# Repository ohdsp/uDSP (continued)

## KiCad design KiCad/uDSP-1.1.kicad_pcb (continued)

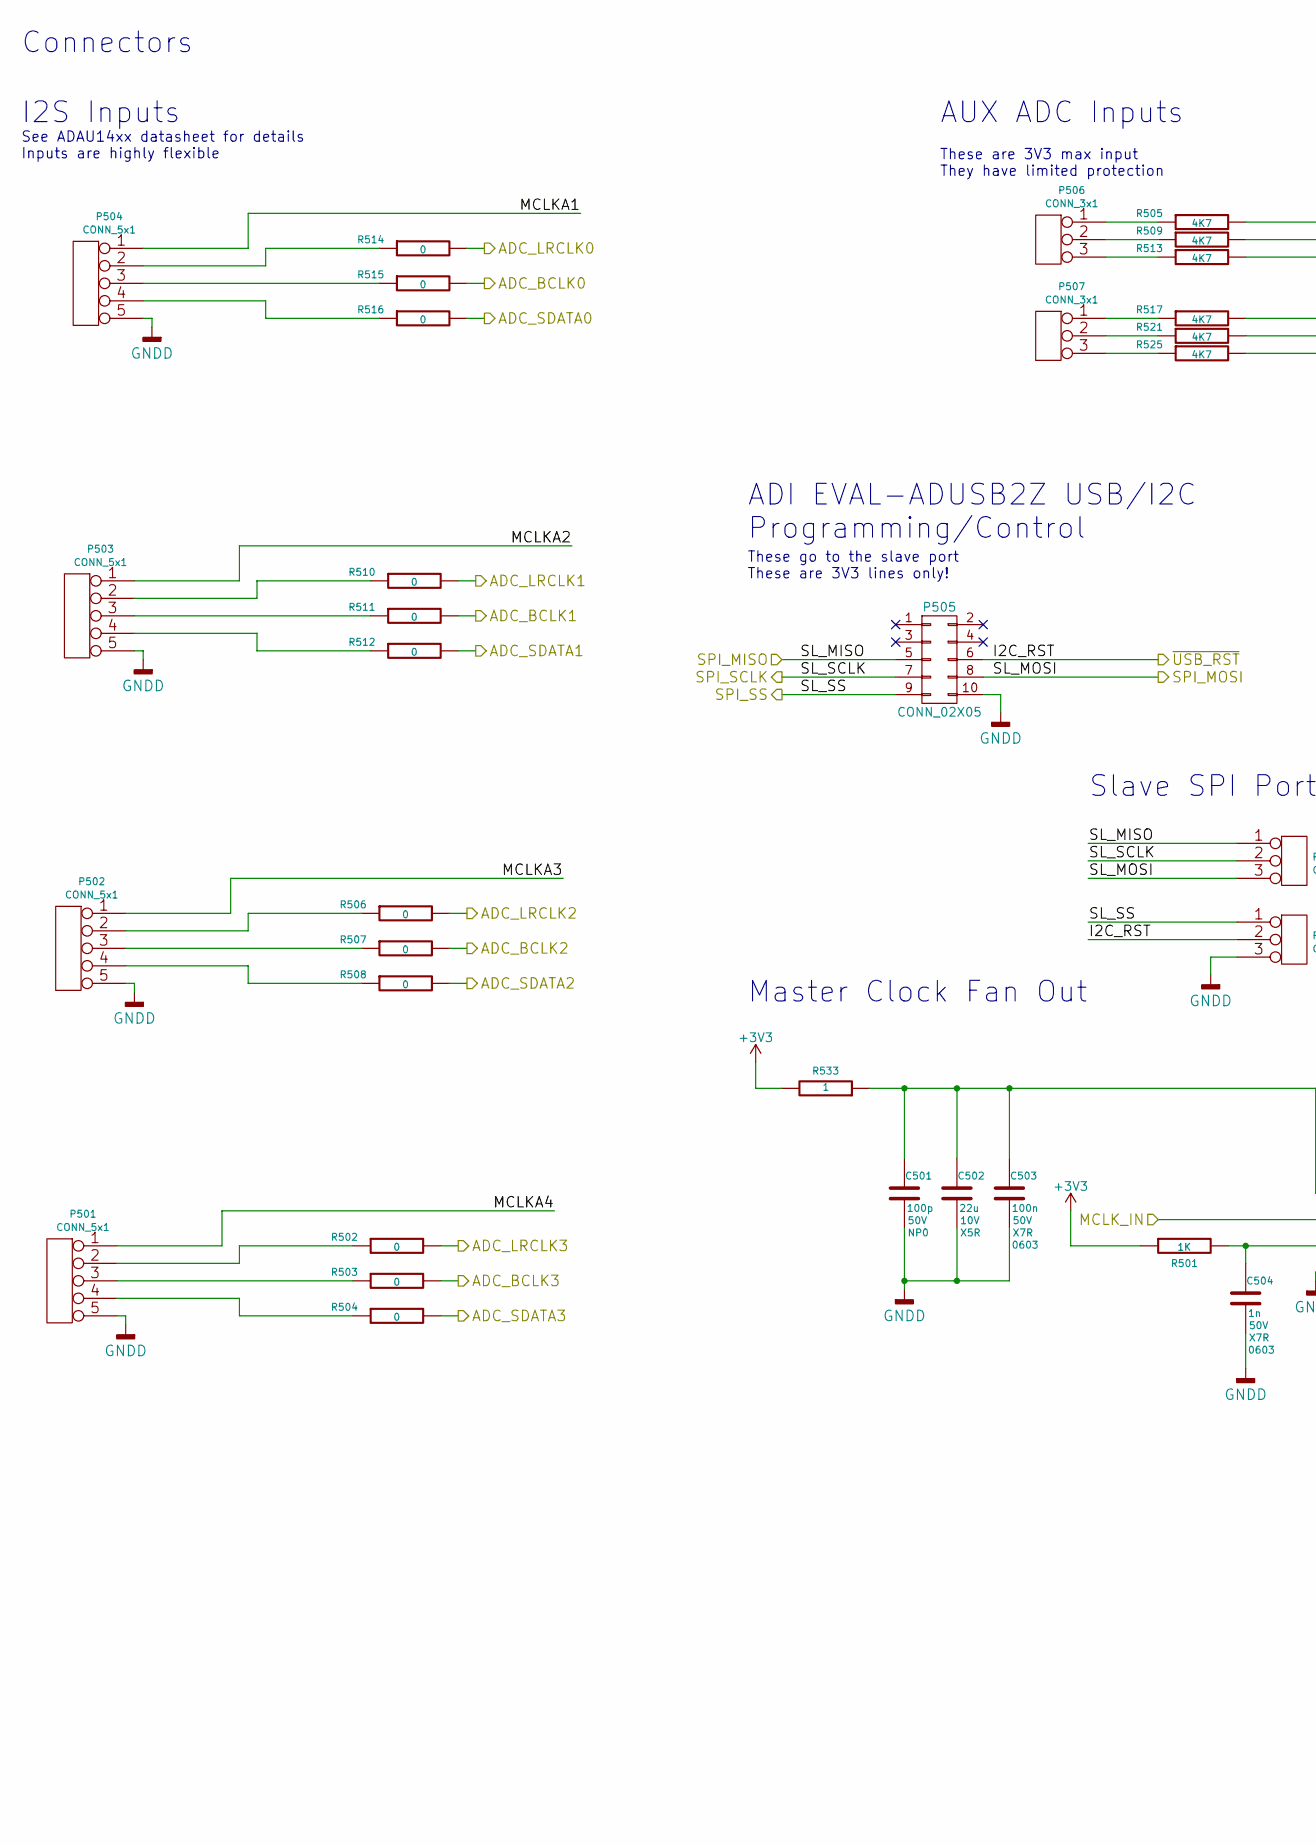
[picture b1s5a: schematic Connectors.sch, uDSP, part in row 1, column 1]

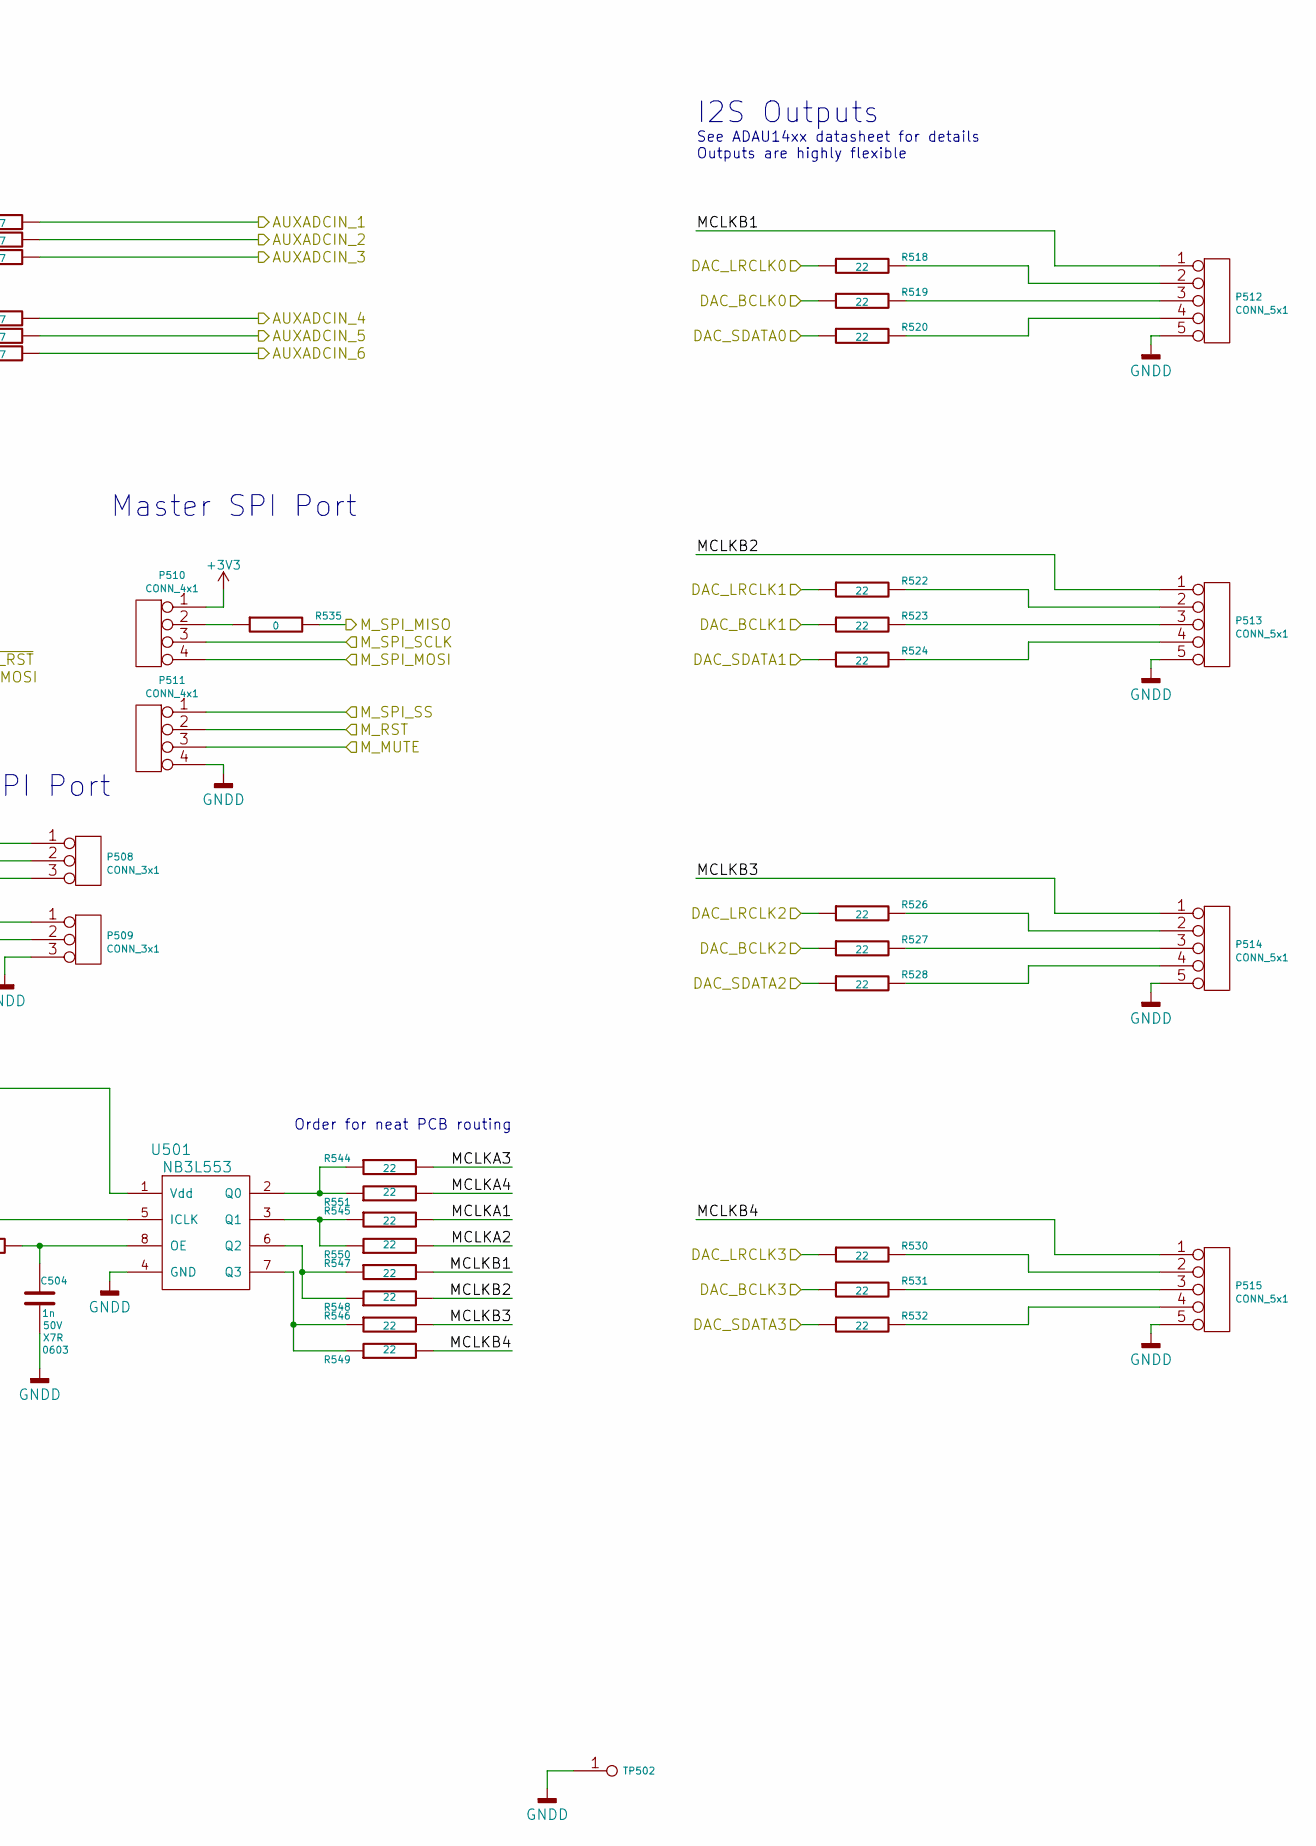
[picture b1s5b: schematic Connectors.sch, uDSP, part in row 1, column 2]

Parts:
C501: 100p; SMD-0603; Voltage 50V; Tolerance 5%
C502: 22u; SMD-0603; Voltage 10V; Tolerance 10%
C503: 100n; SMD-0603; Voltage 50V; Tolerance 10%
C504: 1n; SMD-0603; Voltage 50V; Tolerance 10%
P501, P502, P503, P504, P512, P513, P514, P515: CONN_5x1; CONN_SIL_5_1MM
P505: CONN_02X05; CONN_DIL_2X5_BOX_1MM
P506, P507, P508, P509: CONN_3x1; CONN_SIL_3_1MM
P510, P511: CONN_4x1; CONN_SIL_4_1MM
R501: 1K; SMD-0603; Tolerance 1%
R502, R503, R504, R506, R507, R508, R510, R511, R512, R514, R515, R516, R535: 0; SMD-0603; Tolerance 1%
R505, R509, R513, R517, R521, R525: 4K7; SMD-0603; Tolerance 1%
R518, R519, R520, R522, R523, R524, R526, R527, R528, R530, R531, R532, R544, R545, R546, R547, R548, R549, R550, R551: 22; SMD-0603; Tolerance 1%
R533: 1; SMD-0603; Tolerance 1%
TP502: PIN; TP-TH-1mm
U501: NB3L553; IC_SOIC_8

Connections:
/AUXADC1: R505.2; also elsewhere on the board
/AUXADC2: R509.2; also elsewhere on the board
/AUXADC3: R513.2; also elsewhere on the board
/AUXADC4: R517.2; also elsewhere on the board
/AUXADC5: R521.2; also elsewhere on the board
/AUXADC6: R525.2; also elsewhere on the board
/Connectors/MCLKA1: P504.1, R545.2
/Connectors/MCLKA2: P503.1, R550.2
/Connectors/MCLKA3: P502.1, R544.2
/Connectors/MCLKA4: P501.1, R551.2
/Connectors/MCLKB1: P512.1, R547.2
/Connectors/MCLKB2: P513.1, R548.2
/Connectors/MCLKB3: P514.1, R546.2
/Connectors/MCLKB4: P515.1, R549.2
/GLB_RESET: P511.2; also elsewhere on the board
/IN_BCLK0: R515.2; also elsewhere on the board
/IN_BCLK1: R511.2; also elsewhere on the board
/IN_BCLK2: R507.2; also elsewhere on the board
/IN_BCLK3: R503.2; also elsewhere on the board
/IN_LRCLK0: R514.2; also elsewhere on the board
/IN_LRCLK1: R510.2; also elsewhere on the board
/IN_LRCLK2: R506.2; also elsewhere on the board
/IN_LRCLK3: R502.2; also elsewhere on the board
/IN_SDATA0: R516.2; also elsewhere on the board
/IN_SDATA1: R512.2; also elsewhere on the board
/IN_SDATA2: R508.2; also elsewhere on the board
/IN_SDATA3: R504.2; also elsewhere on the board
/MAN_RESET: P505.6, P509.2; also elsewhere on the board
/MCLK: U501.5 (ICLK); also elsewhere on the board
/OUT_BCLK0: R519.1; also elsewhere on the board
/OUT_BCLK1: R523.1; also elsewhere on the board
/OUT_BCLK2: R527.1; also elsewhere on the board
/OUT_BCLK3: R531.1; also elsewhere on the board
/OUT_LRCLK0: R518.1; also elsewhere on the board
/OUT_LRCLK1: R522.1; also elsewhere on the board
/OUT_LRCLK2: R526.1; also elsewhere on the board
/OUT_LRCLK3: R530.1; also elsewhere on the board
/OUT_SDATA0: R520.1; also elsewhere on the board
/OUT_SDATA1: R524.1; also elsewhere on the board
/OUT_SDATA2: R528.1; also elsewhere on the board
/OUT_SDATA3: R532.1; also elsewhere on the board
/SPI_MISO: P505.5, P508.1; also elsewhere on the board
/SPI_MOSI: P505.8, P508.3; also elsewhere on the board
/SPI_M_CLK: P510.3; also elsewhere on the board
/SPI_M_CS2: P511.1; also elsewhere on the board
/SPI_M_MISO: R535.2; also elsewhere on the board
/SPI_M_MOSI: P510.4; also elsewhere on the board
/SPI_M_MUTE: P511.3; also elsewhere on the board
/SPI_SCLK: P505.7, P508.2; also elsewhere on the board
/SPI_SS: P505.9, P509.1; also elsewhere on the board
GNDD: C501.2, C502.2, C503.2, C504.2, P501.5, P502.5, P503.5, P504.5, P505.10, P509.3, P511.4, P512.5, P513.5, P514.5, P515.5, TP502.1, U501.4 (GND); also elsewhere on the board
unnamed: C501.1, C502.1, C503.1, R533.1, U501.1 (Vdd)
unnamed: C504.1, R501.2, U501.8 (OE)
unnamed: P501.2, R502.1
unnamed: P501.3, R503.1
unnamed: P501.4, R504.1
unnamed: P502.2, R506.1
unnamed: P502.3, R507.1
unnamed: P502.4, R508.1
unnamed: P503.2, R510.1
unnamed: P503.3, R511.1
unnamed: P503.4, R512.1
unnamed: P504.2, R514.1
unnamed: P504.3, R515.1
unnamed: P504.4, R516.1
unnamed: P506.1, R505.1
unnamed: P506.2, R509.1
unnamed: P506.3, R513.1
unnamed: P507.1, R517.1
unnamed: P507.2, R521.1
unnamed: P507.3, R525.1
unnamed: P510.2, R535.1
unnamed: P512.2, R518.2
unnamed: P512.3, R519.2
unnamed: P512.4, R520.2
unnamed: P513.2, R522.2
unnamed: P513.3, R523.2
unnamed: P513.4, R524.2
unnamed: P514.2, R526.2
unnamed: P514.3, R527.2
unnamed: P514.4, R528.2
unnamed: P515.2, R530.2
unnamed: P515.3, R531.2
unnamed: P515.4, R532.2
unnamed: R544.1, R551.1, U501.2 (Q0)
unnamed: R545.1, R550.1, U501.3 (Q1)
unnamed: R546.1, R549.1, U501.7 (Q3)
unnamed: R547.1, R548.1, U501.6 (Q2)

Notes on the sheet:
ADI EVAL-ADUSB2Z USB/I2C Programming/Control
AUX ADC Inputs
These go to the slave port These are 3V3 lines only!
I2S Inputs
See ADAU14xx datasheet for details Inputs are highly flexible
I2S Outputs
These are 3V3 max input They have limited protection
See ADAU14xx datasheet for details Outputs are highly flexible
Order for neat PCB routing
Master Clock Fan Out
Master SPI Port
Slave SPI Port
Connectors

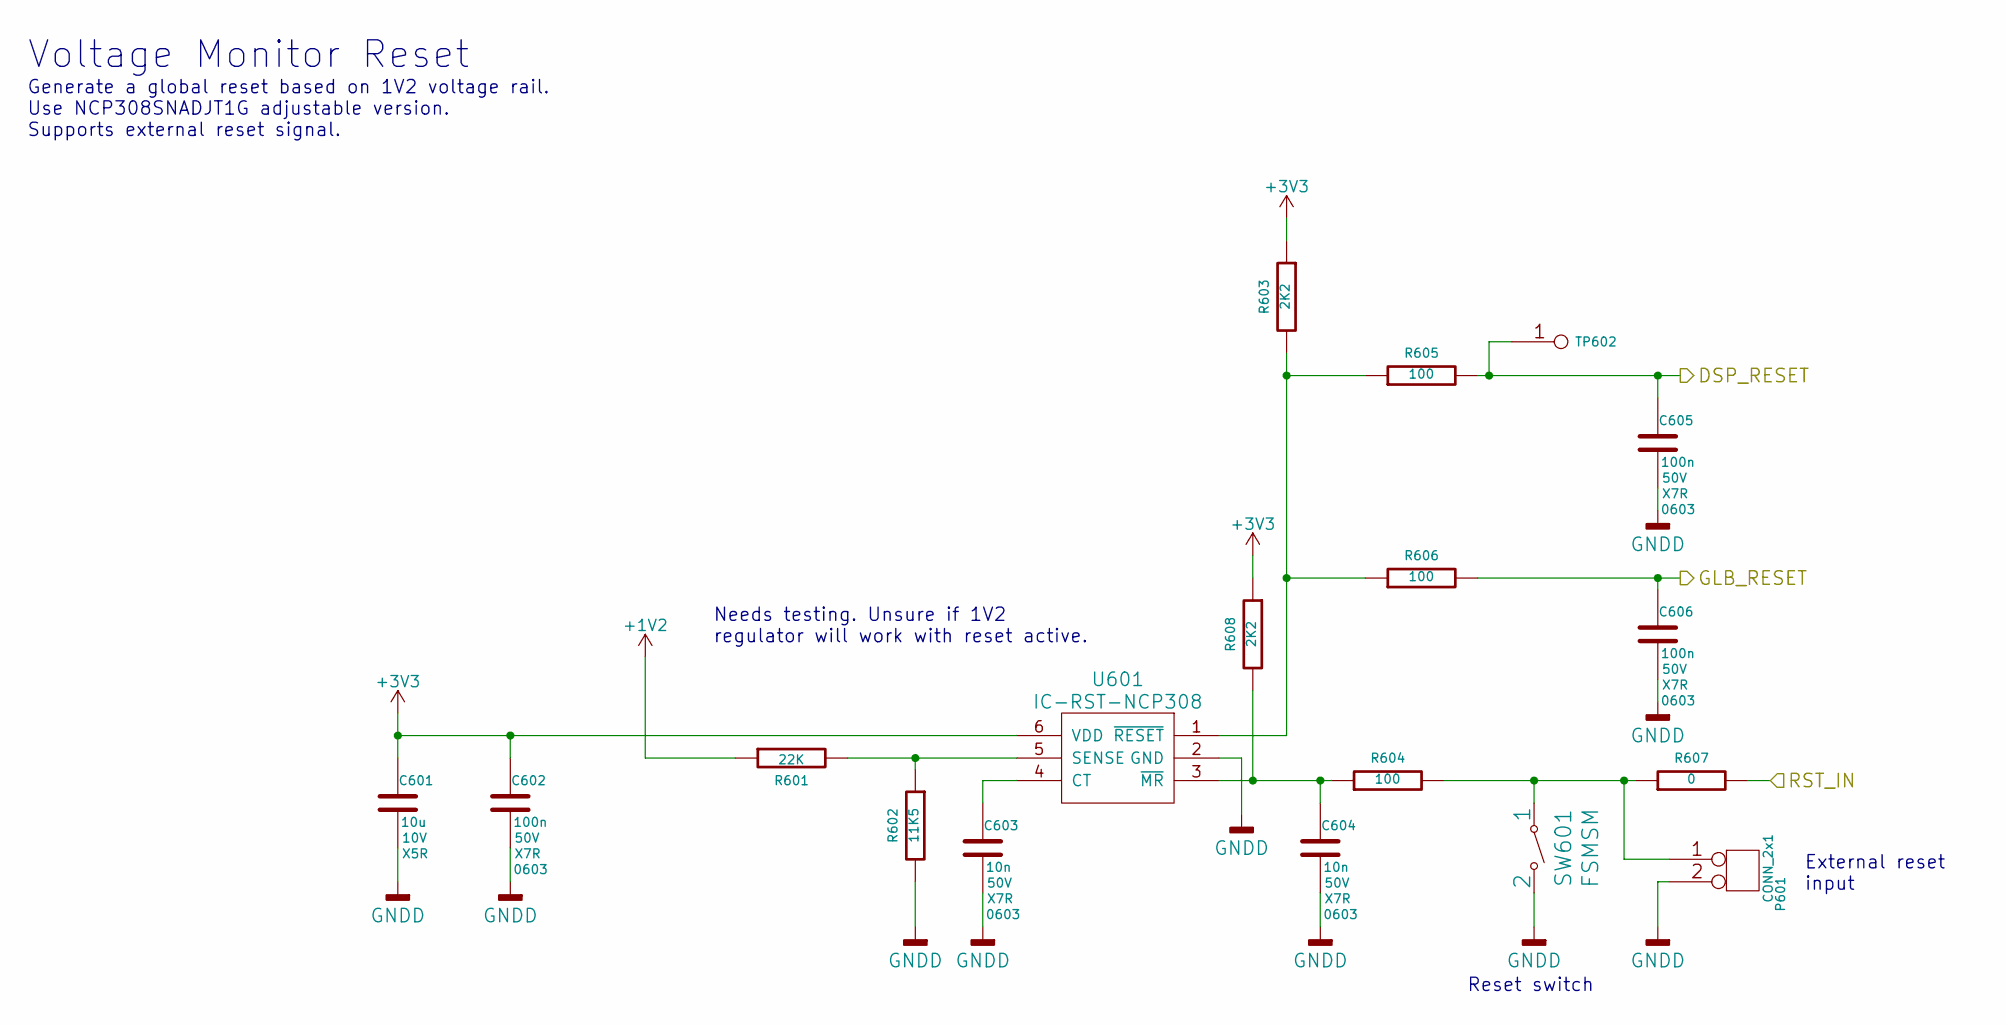
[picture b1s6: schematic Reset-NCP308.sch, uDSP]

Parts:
C601: 10u; SMD-0603; Voltage 10V; Tolerance 20%
C602, C605, C606: 100n; SMD-0603; Voltage 50V; Tolerance 10%
C603, C604: 10n; SMD-0603; Voltage 50V; Tolerance 10%
P601: CONN_2x1; CONN_SIL_2_1MM
R601: 22K; SMD-0603; Tolerance 1%
R602: 11K5; SMD-0603; Tolerance 1%
R603, R608: 2K2; SMD-0603; Tolerance 1%
R604, R605, R606: 100; SMD-0603; Tolerance 1%
R607: 0; SMD-0603; Tolerance 1%
SW601: FSMSM; SW_TACT_SMD_FSMSM
TP602: PIN; TP-1mm
U601: IC-RST-NCP308; IC-SOT23-6

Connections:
+1V2: R601.1; also elsewhere on the board
/DSP_RESET: C605.1, R605.2, TP602.1; also elsewhere on the board
/GLB_RESET: C606.1, R606.2; also elsewhere on the board
/MAN_RESET: R607.2; also elsewhere on the board
GNDD: C601.2, C602.2, C603.2, C604.2, C605.2, C606.2, P601.2, R602.2, SW601.2, U601.2 (GND); also elsewhere on the board
unnamed: C603.1, U601.4 (CT)
unnamed: C604.1, R604.1, R608.2, U601.3 (~MR)
unnamed: P601.1, R604.2, R607.1, SW601.1
unnamed 126: R601.2, R602.1, U601.5 (SENSE); also elsewhere on the board
unnamed: R603.2, R605.1, R606.1, U601.1 (~RESET)

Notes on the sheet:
Generate a global reset based on 1V2 voltage rail. Use NCP308SNADJT1G adjustable version. Supports external reset signal.
Voltage Monitor Reset
External reset input
Needs testing. Unsure if 1V2 regulator will work with reset active.
Reset switch

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
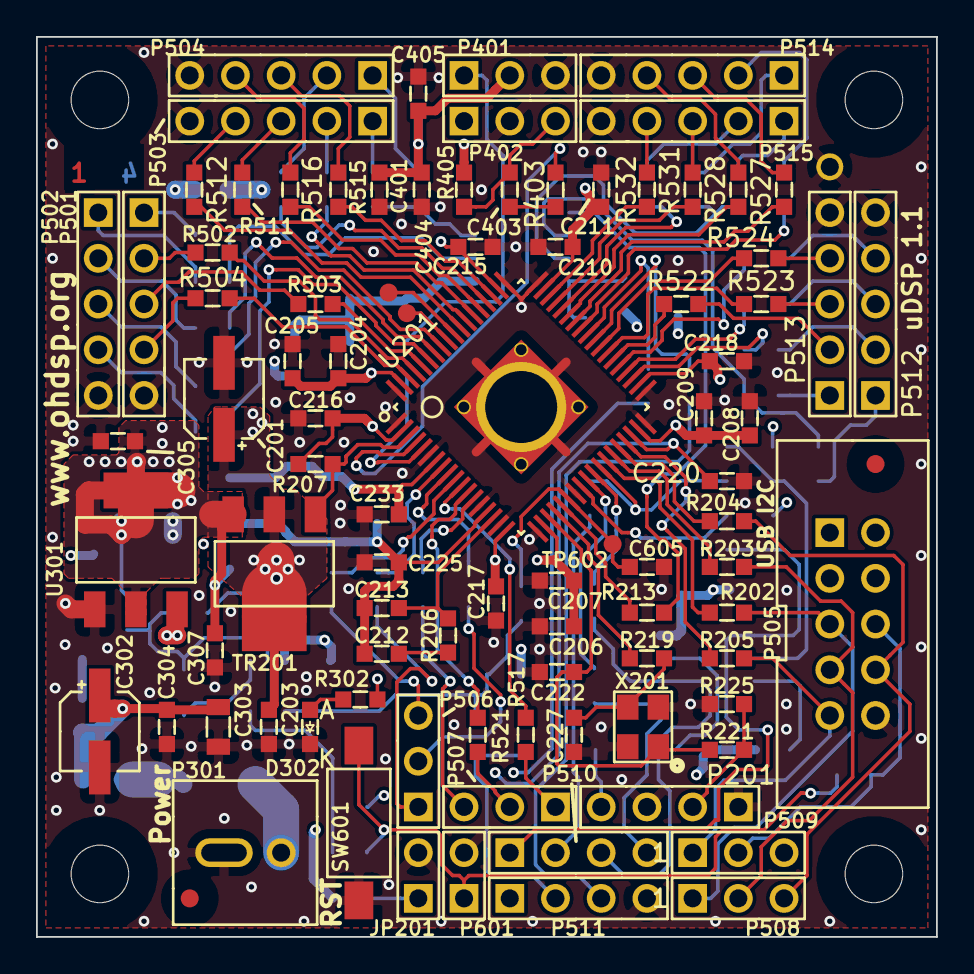
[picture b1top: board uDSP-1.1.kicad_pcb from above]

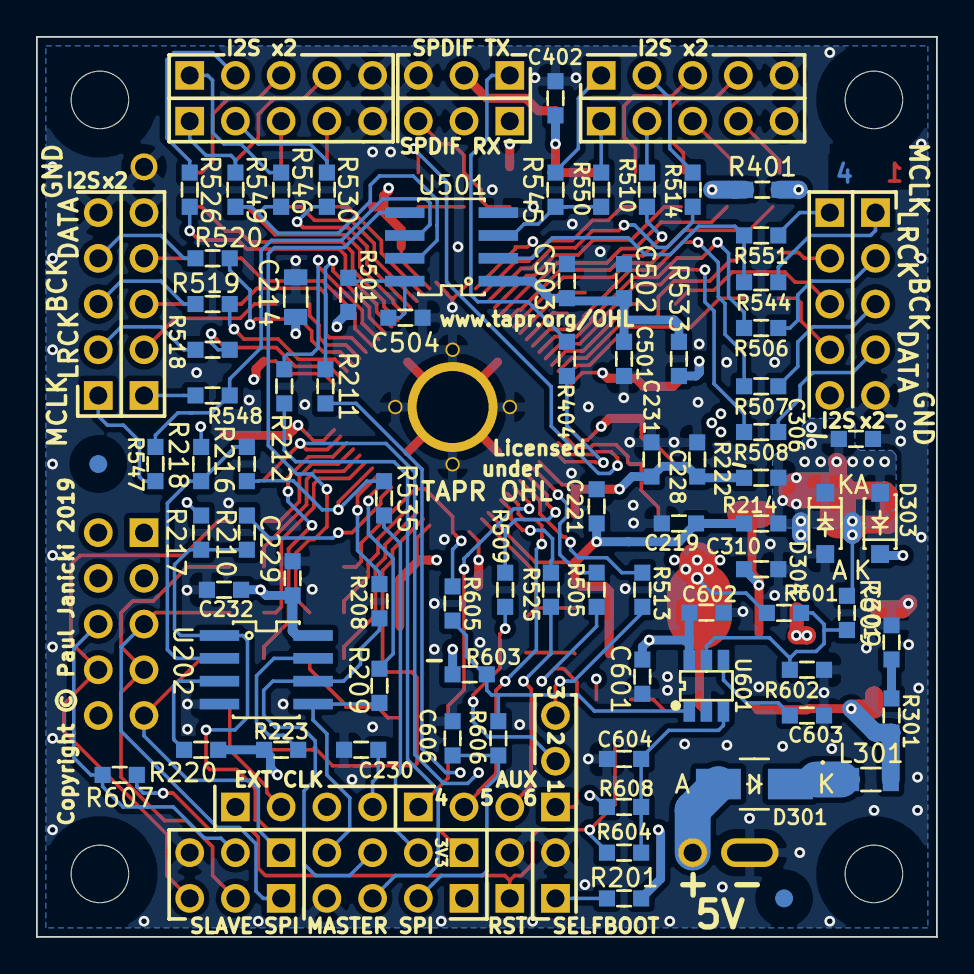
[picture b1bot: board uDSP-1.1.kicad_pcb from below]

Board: 4 copper layers, 50.0 x 50.0 mm, 177 parts (80 on the bottom side), 133 nets.

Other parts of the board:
R609: N/F; SMD-0603

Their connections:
unnamed 126: R609.2; also elsewhere on the board

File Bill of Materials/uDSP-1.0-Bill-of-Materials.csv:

Reference; Quantity; Footprint; Value; Description; Type; Voltage; Size; Tolerance; Power; Current; 
C201 ;1;CAP-SMD-SIZE-B;22u;'Low impedance aluminium electrolytic capacitor - Panasonic FP, FK or Similar;'Case B SMD Aluminium Electrolytic;'6V3;';';';';
C203 C204 C206 C208 C210 C215 C216 C217 C218 C225 C229 C230 C233 C304 C305 C307 C404 C405 C503 C602 C605 C606 ;22;SMD-0603;100n;'Ceramic capacitor;'X7R;'50V;'0603;'10%;';';
C205 C207 C209 C211 C220 C403 C603 C604 ;8;SMD-0603;10n;'Ceramic capacitor;'X7R;'50V;'0603;'10%;';';
C212 ;1;SMD-0603;5n6;'Ceramic capacitor;'X7R;'50V;'0603;'10%;';';
C213 ;1;SMD-0603;150p;'Ceramic capacitor;'C0G;'50V;'0603;'5%;';';
C214 ;1;SMD-0805;10u;'Ceramic capacitor;'X5R;'10V;'0805;'20%;';';
C219 C228 C301 C401 C501 ;5;SMD-0603;100p;'Ceramic capacitor;'NP0;'50V;'0603;'5%;';';
C221 C231 C232 ;3;SMD-0603;10u;'Ceramic capacitor;'X5R;'10V;'0603;'10%;';';
C222 C227 ;2;SMD-0603;33p;'Ceramic capacitor;'C0G;'25V;'0603;'5%;';';
C302 ;1;CAP-SMD-SIZE-B;10u;'Low impedance aluminium electrolytic capacitor - Panasonic FP, FK or Similar;'Case B SMD Aluminium Electrolytic;'10V;';';';';
C303 ;1;SMD-0805;22u;'Ceramic capacitor;'X5R;'25V;'0805;'20%;';';
C306 ;1;SMD-0603;22u;'Ceramic capacitor;'X5R;'10V;'0603;'20%;';';
C310 C601 ;2;SMD-0603;10u;'Ceramic capacitor;'X5R;'10V;'0603;'20%;';';
C402 C502 ;2;SMD-0603;22u;'Ceramic capacitor;'X5R;'10V;'0603;'10%;';';
C504 ;1;SMD-0603;1n;'Ceramic capacitor;'X7R;'50V;'0603;'10%;';';
D301 ;1;DIODE-SMA;B240A;'B240A 2A 40V Schottky Rectifier - SMA (DO-214AC);';';';';';';
D302 ;1;SMD-0603-LED;LED 0603;'LED - SMD - Vf 1.8V to 2.2V;';';'0603;';';';
D303 D304 ;2;DIODE-SOD-123;1N5819HW;'1A 40V Schottky Rectifier - SOD-123;';';';';';';
FID301 FID302 FID303 FID304 ;4;FID-1MM-3MM;MNT_HOLE;'1mm fiducial;';';';';';';
JP201 P601 ;2;CONN_SIL_2_1MM;CONN_2x1;'1x2 2.54mm pitch pin header;';';';';';';
L301 ;1;SMD-0805;600R@100MHz;'Ferrite bead, current rating 1A or higher, 600R@100MHz;';';'0805;';';'=>2A;
MNT301 MNT302 MNT303 MNT304 ;4;MNT_HOLE_3.2mm;MNT_HOLE;'3.2mm mounting hole;';';';';';';
P201 P510 P511 ;3;CONN_SIL_4_1MM;CONN_4x1;'1x4 2.54mm pitch pin header;';';';';';';
P301 ;1;CONN-2WAY-2.54mm-3.81mm-SPACING;CONN_2x1;'2 way screw terminal, any 2.54mm to 3.81mm pitch part;';';';';';';
P401 P402 P506 P507 P508 P509 ;6;CONN_SIL_3_1MM;CONN_3x1;'1x3 2.54mm pitch pin header;';';';';';';
P505 ;1;CONN_DIL_2X5_BOX_1MM;CONN_02X05;'2x5 2.54mm pitch box header;';';';';';';
P501 P502 P503 P504 P512 P513 P514 P515 ;8;CONN_SIL_5_1MM;CONN_5x1;'1x5 2.54mm pitch pin header;';';';';';';
R202 R208 R209 R210 R211 R212 R213 R216 R403 R404 R518 R519 R520 R522 R523 R524 R526 R527 R528 R530 R531 R532 R544 R545 R546 R547 R548 R549 R550 R551 ;30;SMD-0603;22;'Thick or thin film resistor;';';'0603;'1%;'63mW;';
R203 R204 R205 R502 R503 R504 R506 R507 R508 R510 R511 R512 R514 R515 R516 R535 R607 ;17;SMD-0603;0;'Thick or thin film resistor;';';'0603;'1%;'63mW;';
R206 ;1;SMD-0603;4k3;'Thick or thin film resistor;';';'0603;'1%;'63mW;';
R201 R207 R501 ;3;SMD-0603;1K;'Thick or thin film resistor;';';'0603;'1%;'63mW;';
R214 R222 R401 R533 ;4;SMD-0603;1;'Thick or thin film resistor;';';'0603;'1%;'63mW;';
R217 R220 R223 R405 ;4;SMD-0603;10K;'Thick or thin film resistor;';';'0603;'1%;'63mW;';
R219 R604 R605 R606 ;4;SMD-0603;100;'Thick or thin film resistor;';';'0603;'1%;'63mW;';
R218 R221 R225 ;3;SMD-0603;N/F;'Thick or thin film resistor;';';'0603;'1%;'63mW;';
R301 ;1;SMD-0603;47;'Thick or thin film resistor;';';'0603;'1%;'63mW;';
R302 ;1;SMD-0603;470;'Thick or thin film resistor;';';'0603;'1%;'63mW;';
R505 R509 R513 R517 R521 R525 ;6;SMD-0603;4K7;'Thick or thin film resistor;';';'0603;'1%;'63mW;';
R601 ;1;SMD-0603;22K;'Thick or thin film resistor;';';'0603;'1%;'63mW;';
R602 ;1;SMD-0603;11K5;'Thick or thin film resistor;';';'0603;'1%;'63mW;';
R603 R608 ;2;SMD-0603;2K2;'Thick or thin film resistor;';';'0603;'1%;'63mW;';
SW601 ;1;SW_TACT_SMD_FSMSM;FSMSM;'3.5mm x 6mm SMD tactile switch - e.g. Alcoswitch FSMSM;';';';';';';
TP201 TP202 TP602 ;3;TP-1mm;PIN;
TP502 ;1;TP-TH-1mm;PIN;
TR201 ;1;IC-SOT-223;NJT4030PT3G;'On Semi NJT4030PT3G PNP Transistor (min 2W, 200hFE, 2A);';';';';';';
U201 ;1;IC-LFCSP72-HANDFIT;ADAU1452WBCPZ;'SigmaDSP Digital Audio Processor - Use ADAU1462, ADAU1466, ADAU1452, ADAU1451, or ADAU1450;';';';';';';
U202 ;1;IC_SOIC_8;M95M01-RMN6TP;'1 Mbit SPI Bus Serial EEPROM - 8 pin SOIC;';';';';';';
U301 ;1;IC-SOT-223;TLV1117LV33DCY;'TLV1117LV 1-A, Positive Fixed-Voltage, Low-Dropout Regulator - Fixed 3V3;';';';';';';
U501 ;1;IC_SOIC_8;NB3L553;'On Semi - 1:4 Clock Fanout Buffer;';';';';';';
U601 ;1;IC-SOT23-6;IC-RST-NCP308;'On Semi NCP308 SOT-23-6 TSOP-6 Supervisor;';';';';';';
X201 ;1;XTAL_3.2x2.5_4PIN;24M576;'Crystal 3.2mm x 2.5mm - eg Abracon ASE-24.576MHZ-LC-T;';';';';';';

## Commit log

2019-03-11 uDSP-1.0
    Revision 1.0 release
2019-03-11 Cleanup
2019-04-02 uDSP 1.1
    uDSP 1.1
    Add CS1 and CS2 to SPI headers - removed 3V3 power
    Add 3V3 monitor option to reset circuit
